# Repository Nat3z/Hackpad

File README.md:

# Nat3z HackPad - TetoBoard

This is the very rudimentary HackPad is created for Highway qualification. It includes a Rotary
Encoder, 3 Cherry MX Switches, and finally, the RP2040!

[Devlog](./Devlog.md)
[Bill of Materials](./BOM.md)

## Images

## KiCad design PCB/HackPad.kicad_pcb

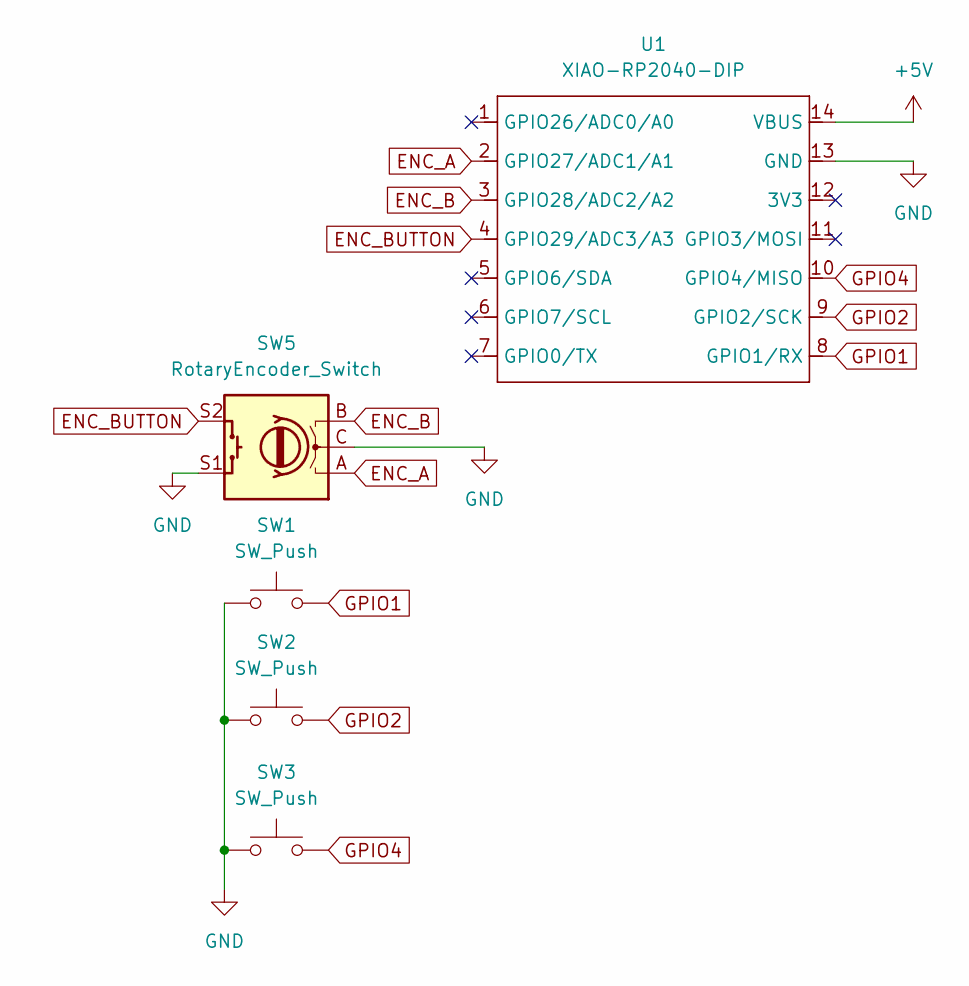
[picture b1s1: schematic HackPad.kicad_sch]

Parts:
SW1, SW2, SW3: SW_Push; SW_Cherry_MX_1.00u_PCB
SW5: RotaryEncoder_Switch; RotaryEncoder_Alps_EC11E-Switch_Vertical_H20mm
U1: XIAO-RP2040-DIP

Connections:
+5V: U1.14 (VBUS)
ENC_A: SW5.A, U1.2 (GPIO27/ADC1/A1)
ENC_B: SW5.B, U1.3 (GPIO28/ADC2/A2)
ENC_BUTTON: SW5.S2, U1.4 (GPIO29/ADC3/A3)
GND: SW1.1, SW2.1, SW3.1, SW5.C, SW5.S1, U1.13 (GND)
GPIO1: SW1.2, U1.8 (GPIO1/RX)
GPIO2: SW2.2, U1.9 (GPIO2/SCK)
GPIO4: SW3.2, U1.10 (GPIO4/MISO)

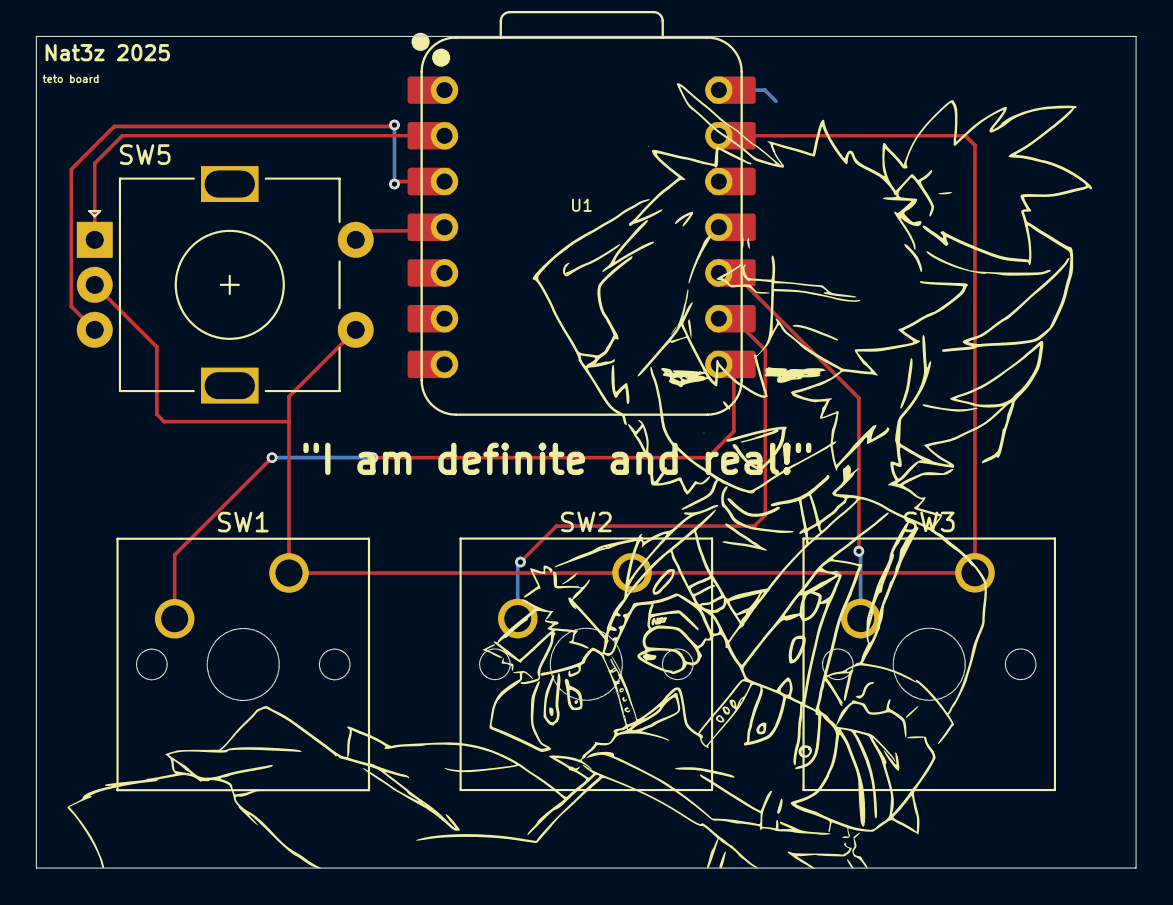
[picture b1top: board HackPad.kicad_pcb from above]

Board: 2 copper layers, 61.1 x 46.2 mm, 5 parts (0 on the bottom side), 7 nets.

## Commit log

2025-06-25 teto board
2025-06-27 final commit :)
2025-06-28 added to pass verification
